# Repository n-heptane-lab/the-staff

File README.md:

The Staff
=========

A simple wizard staff based around a Teensy 3.1 and a neopixel strand.

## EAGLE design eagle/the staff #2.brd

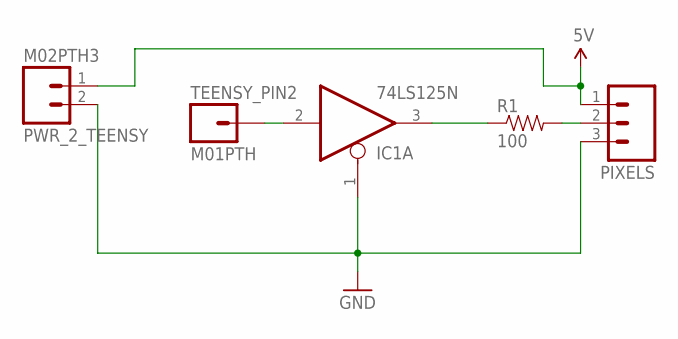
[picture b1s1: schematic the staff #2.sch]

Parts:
IC1: 74LS125N; DIL14
PIXELS: M03LONGPADS; 1X03_LONGPADS
PWR_2_TEENSY: M02PTH3; 1X02_LONGPADS
R1: 100; AXIAL-0.4
TEENSY_PIN2: M01PTH; 1X01

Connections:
GND: IC1.1 (OE), IC1.7 (GND), PIXELS.3, PWR_2_TEENSY.2
unnamed: IC1.3 (O), R1.P$1 (1)
unnamed: PIXELS.2, R1.P$2 (2)
unnamed: IC1.2 (I), TEENSY_PIN2.1
VCC: IC1.14 (VCC), PIXELS.1, PWR_2_TEENSY.1

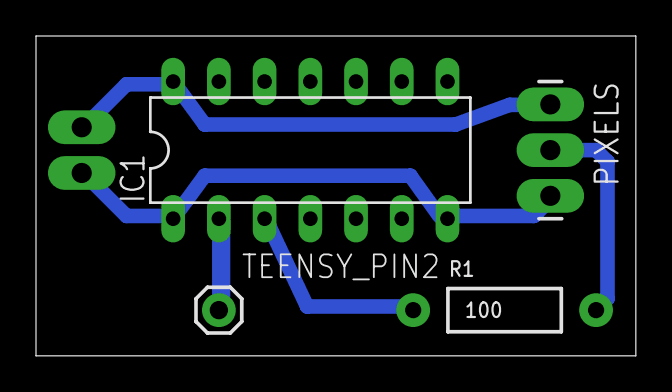
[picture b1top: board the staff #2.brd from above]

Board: 2 copper layers, 33.3 x 17.8 mm, 5 parts (0 on the bottom side), 5 nets.

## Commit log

2014-10-27 added a board with out the capacitor

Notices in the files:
parts and their libraries:
SparkFun-Connectors: Licensing: Creative Commons ShareAlike 4.0 International - https://creativecommons.org/licenses/by-sa/4.0
